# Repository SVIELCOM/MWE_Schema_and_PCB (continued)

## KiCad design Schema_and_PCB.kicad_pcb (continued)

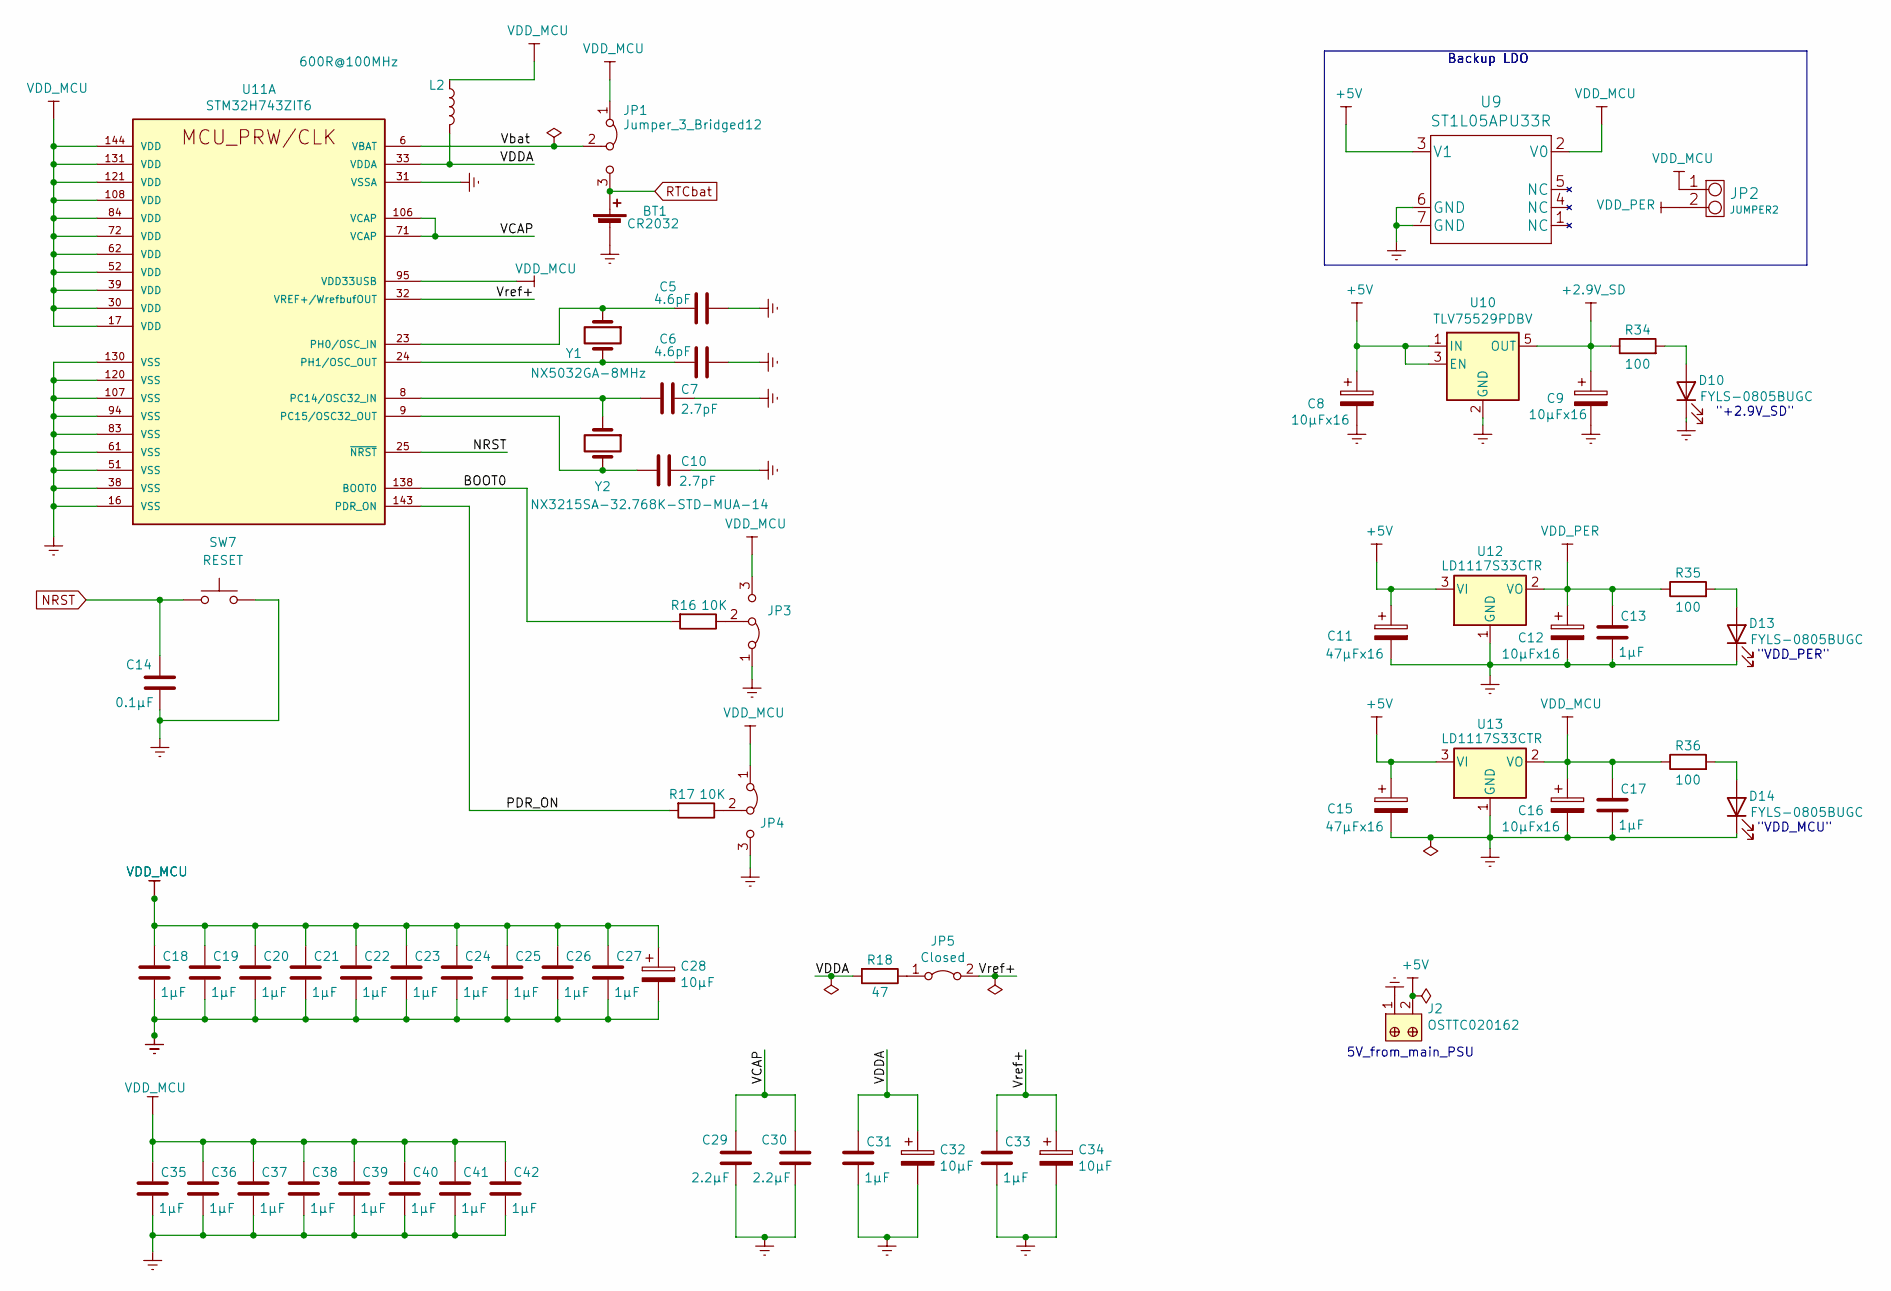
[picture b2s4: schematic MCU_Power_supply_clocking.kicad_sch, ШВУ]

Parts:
BT1: CR2032; BAT_BS-7
C5, C6: 4.6pF; C_0603_1608Metric_Pad1.08x0.95mm_HandSolder
C7, C10: 2.7pF; C_0603_1608Metric_Pad1.08x0.95mm_HandSolder
C8, C9, C12, C16: 10µFx16; CP_EIA-3216-10_Kemet-I
C11, C15: 47µFx16; CP_EIA-7343-31_Kemet-D_Pad2.25x2.55mm_HandSolder
C13, C17, C18, C19, C20, C21, C22, C23, C24, C25, C26, C27, C31, C33, C35, C36, C37, C38, C39, C40, C41, C42: 1µF; C_0603_1608Metric_Pad1.08x0.95mm_HandSolder
C14: 0.1µF; C_0603_1608Metric_Pad1.08x0.95mm_HandSolder
C28, C32, C34: 10µF; CP_EIA-3216-10_Kemet-I
C29, C30: 2.2µF; C_0603_1608Metric_Pad1.08x0.95mm_HandSolder
D10, D13, D14: FYLS-0805BUGC; LED_0805_2012Metric
J2: OSTTC020162; Term_Block_1x2_P5mm; MPN OSTTC020162; Digi-Key_PN ED2600-ND
JP1, JP4: Jumper_3_Bridged12; SolderJumper-3_P1.3mm_Open_RoundedPad1.0x1.5mm_NumberLabels
JP2: JUMPER2; PinHeader_1x02_P2.54mm_Vertical
JP3: BOOT0; PinHeader_1x03_P2.54mm_Horizontal
JP5: Closed; SolderJumper-2_P1.3mm_Open_RoundedPad1.0x1.5mm
L2: 600R@100MHz; L_0805_2012Metric_Pad1.15x1.40mm_HandSolder
R16, R17: 10K; R_0805_2012Metric_Pad1.20x1.40mm_HandSolder
R18: 47; R_0805_2012Metric_Pad1.20x1.40mm_HandSolder
R34, R35, R36: 100; R_0805_2012Metric
SW7: RESET; SW_PUSH_6mm
U9: ST1L05APU33R
U10: TLV75529PDBV; SOT-23-5
U11: STM32H743ZIT6; QFP50P2200X2200X160-144N; PARTREV 7
U12, U13: LD1117S33CTR; SOT-223-3_TabPin2
Y1: NX5032GA-8MHz; Crystal_SMD_5032-2Pin_5.0x3.2mm
Y2: NX3215SA-32.768K-STD-MUA-14; Crystal_SMD_MicroCrystal_CC7V-T1A-2Pin_3.2x1.5mm_HandSolder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

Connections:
+2,9V: C9.1, R34.1, U10.5 (OUT); also elsewhere on the board
/MCU_Power_supply_clocking/BOOT0: R16.2, U11.138 (BOOT0)
/MCU_Power_supply_clocking/PDR_ON: R17.2, U11.143 (PDR_ON)
/MCU_Power_supply_clocking/VCAP: C29.2, C30.2, U11.71 (VCAP), U11.106 (VCAP)
/MCU_Power_supply_clocking/VDDA: C31.1, C32.1, L2.2, R18.2, U11.33 (VDDA)
/MCU_Power_supply_clocking/Vbat: JP1.2 (C), U11.6 (VBAT)
/MCU_Power_supply_clocking/Vref+: C33.1, C34.1, JP5.2 (B), U11.32 (VREF+/WrefbufOUT)
GNDREF: BT1.2 (-), C5.1, C6.1, C7.1, C8.2, C9.2, C10.1, C11.2, C12.2, C13.2, C14.1, C15.2, C16.2, C17.2, C18.2, C19.2, C20.2, C21.2, C22.2, C23.2, C24.2, C25.2, C26.2, C27.2, C28.2, C29.1, C30.1, C31.2, C32.2, C33.2, C34.2, C35.2, C36.2, C37.2, C38.2, C39.2, C40.2, C41.2, C42.2, D10.1 (K), D13.1 (K), D14.1 (K), J2.1, JP3.1 (A), JP4.3 (B), SW7.2, U9.6 (GND), U9.7 (GND), U10.2 (GND), U11.16 (VSS), U11.31 (VSSA), U11.38 (VSS), U11.51 (VSS), U11.61 (VSS), U11.83 (VSS), U11.94 (VSS), U11.107 (VSS), U11.120 (VSS), U11.130 (VSS), U12.1 (GND), U13.1 (GND); also elsewhere on the board
NRST: C14.2, SW7.1, U11.25 (~NRST); also elsewhere on the board
unnamed: C5.2, U11.23 (PH0/OSC_IN), Y1.1
unnamed: C6.2, U11.24 (PH1/OSC_OUT), Y1.2
unnamed: C7.2, U11.8 (PC14/OSC32_IN), Y2.1
unnamed: C10.2, U11.9 (PC15/OSC32_OUT), Y2.2
unnamed: D10.2 (A), R34.2
unnamed: D13.2 (A), R35.2
unnamed: D14.2 (A), R36.2
unnamed: JP3.2 (C), R16.1
unnamed: JP4.2 (C), R17.1
unnamed: JP5.1 (A), R18.1
RTCbat: BT1.1 (+), JP1.3 (B); also elsewhere on the board
VDD_MCU: C16.1, C17.1, C18.1, C19.1, C20.1, C21.1, C22.1, C23.1, C24.1, C25.1, C26.1, C27.1, C28.1, C35.1, C36.1, C37.1, C38.1, C39.1, C40.1, C41.1, C42.1, JP1.1 (A), JP2.1, JP3.3 (B), JP4.1 (A), L2.1, R36.1, U9.2 (V0), U11.17 (VDD), U11.30 (VDD), U11.39 (VDD), U11.52 (VDD), U11.62 (VDD), U11.72 (VDD), U11.84 (VDD), U11.95 (VDD33USB), U11.108 (VDD), U11.121 (VDD), U11.131 (VDD), U11.144 (VDD), U13.2 (VO); also elsewhere on the board
VDD_PER: C12.1, C13.1, JP2.2, R35.1, U12.2 (VO); also elsewhere on the board

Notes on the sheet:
Backup LDO
5V_from_main_PSU
"VDD_PER"
"+2.9V_SD"
"VDD_MCU"

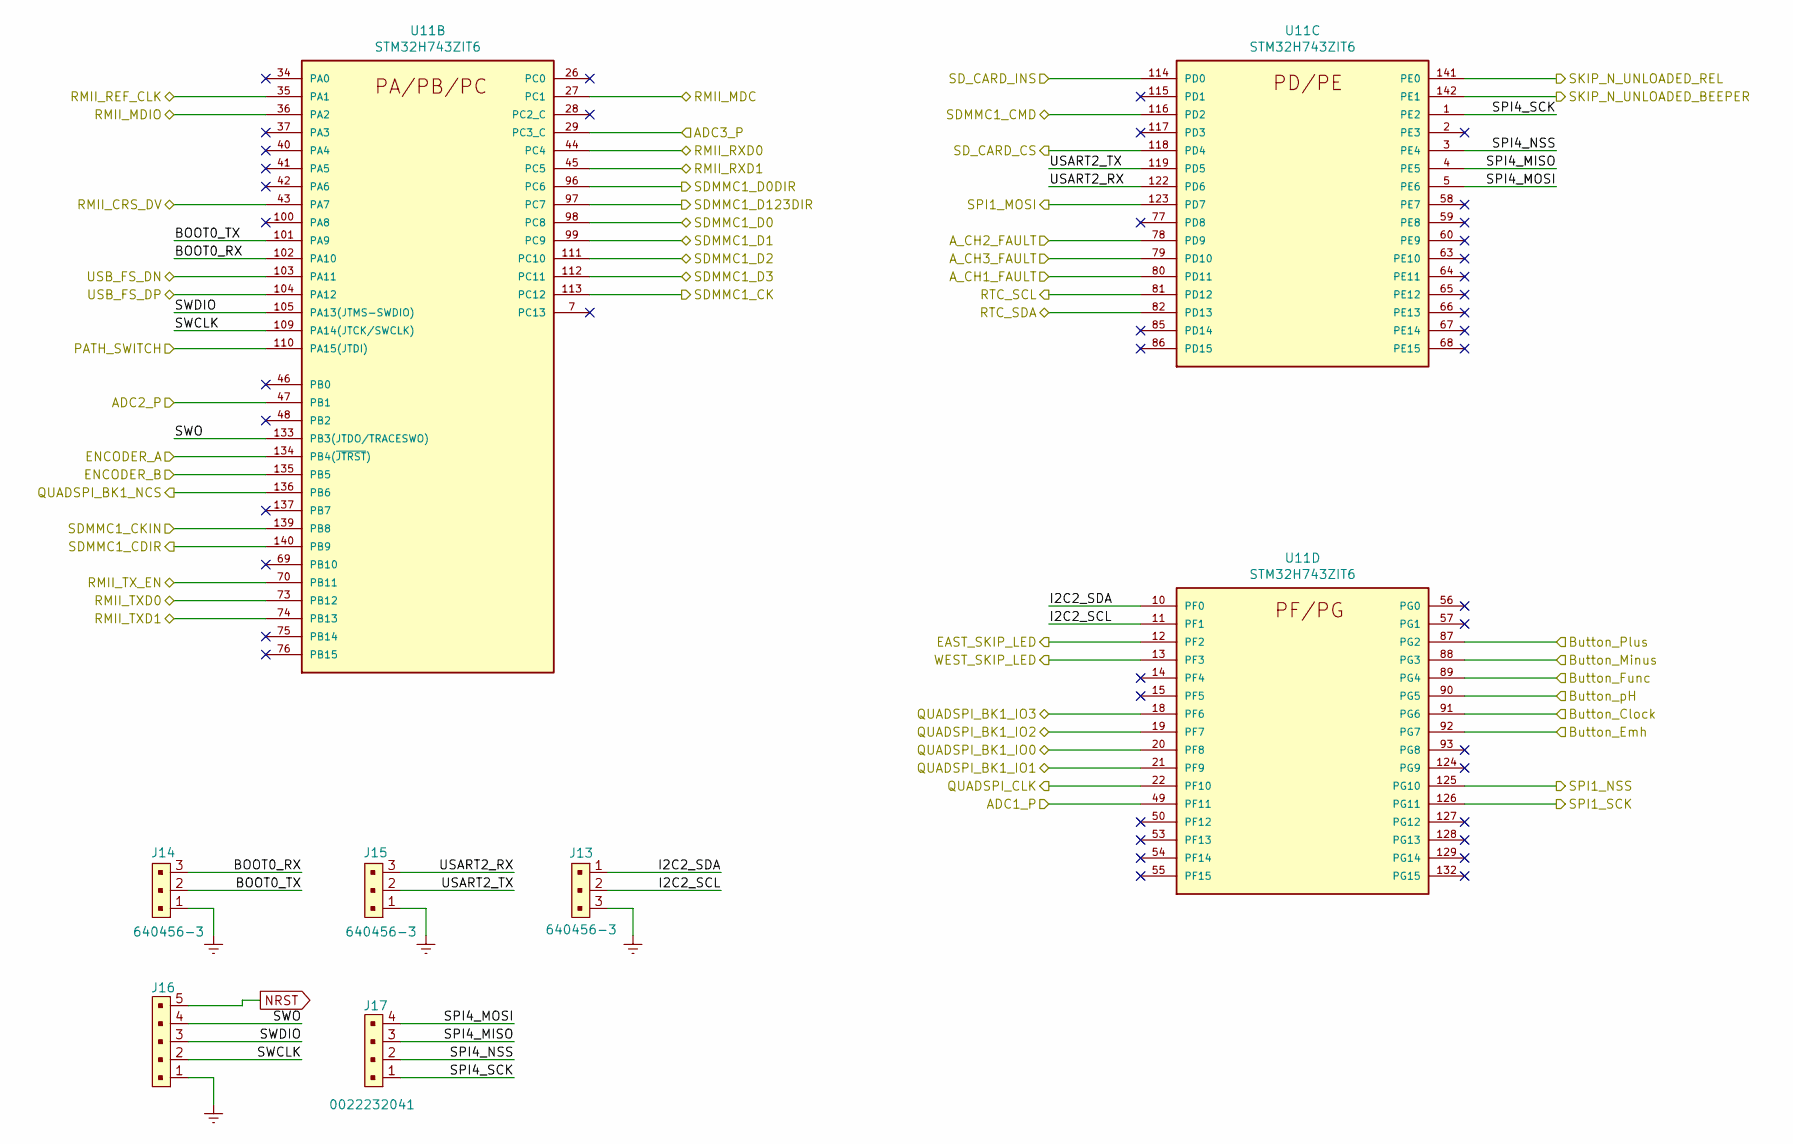
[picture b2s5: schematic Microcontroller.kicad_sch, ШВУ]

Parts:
J13, J14, J15: 640456-3; PinHeader_1x03_P2.54mm_Vertical; MPN 640456-3; Digi-Key_PN A19470-ND
J16: B5B-XH-A_LF__SN_; PinHeader_1x05_P2.54mm_Vertical; MPN B5B-XH-A(LF)(SN); Digi-Key_PN 455-2270-ND
J17: 0022232041; PinHeader_1x04_P2.54mm_Vertical; MPN 0022232041; Digi-Key_PN WM4202-ND
U11: STM32H743ZIT6; QFP50P2200X2200X160-144N; PARTREV 7

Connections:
/Buttons/Button_Clock: U11.91 (PG6); also elsewhere on the board
/Buttons/Button_Emh: U11.92 (PG7); also elsewhere on the board
/Buttons/Button_Func: U11.89 (PG4); also elsewhere on the board
/Buttons/Button_Minus: U11.88 (PG3); also elsewhere on the board
/Buttons/Button_Plus: U11.87 (PG2); also elsewhere on the board
/Buttons/Button_pH: U11.90 (PG5); also elsewhere on the board
/Digital_IO_analog_Inputs/ADC1_P: U11.49 (PF11); also elsewhere on the board
/Digital_IO_analog_Inputs/ADC2_P: U11.47 (PB1); also elsewhere on the board
/Digital_IO_analog_Inputs/ADC3_P: U11.29 (PC3_C); also elsewhere on the board
/Digital_IO_analog_Inputs/A_CH1_FAULT: U11.77 (PD8); also elsewhere on the board
/Digital_IO_analog_Inputs/A_CH2_FAULT: U11.75 (PB14); also elsewhere on the board
/Digital_IO_analog_Inputs/A_CH3_FAULT: U11.76 (PB15); also elsewhere on the board
/Digital_IO_analog_Inputs/ENCODER_A: U11.134 (PB4(~JTRST)); also elsewhere on the board
/Digital_IO_analog_Inputs/ENCODER_B: U11.135 (PB5); also elsewhere on the board
/Digital_IO_analog_Inputs/LEVEL_SWITCH: U11.110 (PA15(JTDI)); also elsewhere on the board
/Digital_IO_analog_Inputs/SKIP_N_UNLOADED_BEEPER: U11.142 (PE1); also elsewhere on the board
/Digital_IO_analog_Inputs/SKIP_N_UNLOADED_REL: U11.141 (PE0); also elsewhere on the board
/Indicator/EAST_SKIP_LED: U11.12 (PF2); also elsewhere on the board
/Indicator/SPI1_MOSI: U11.123 (PD7); also elsewhere on the board
/Indicator/SPI1_NSS: U11.125 (PG10); also elsewhere on the board
/Indicator/SPI1_SCK: U11.126 (PG11); also elsewhere on the board
/Indicator/WEST_SKIP_LED: U11.13 (PF3); also elsewhere on the board
/LAN/RMII_CRS_DV: U11.43 (PA7); also elsewhere on the board
/LAN/RMII_MDC: U11.27 (PC1); also elsewhere on the board
/LAN/RMII_MDIO: U11.36 (PA2); also elsewhere on the board
/LAN/RMII_REF_CLK: U11.35 (PA1); also elsewhere on the board
/LAN/RMII_RXD0: U11.44 (PC4); also elsewhere on the board
/LAN/RMII_RXD1: U11.45 (PC5); also elsewhere on the board
/LAN/RMII_TXD0: U11.73 (PB12); also elsewhere on the board
/LAN/RMII_TXD1: U11.74 (PB13); also elsewhere on the board
/LAN/RMII_TX_EN: U11.70 (PB11); also elsewhere on the board
/Microcontroller/BOOT0_RX: J14.3, U11.102 (PA10)
/Microcontroller/BOOT0_TX: J14.2, U11.101 (PA9)
/Microcontroller/I2C2_SCL: J13.2, U11.11 (PF1)
/Microcontroller/I2C2_SDA: J13.1, U11.10 (PF0)
/Microcontroller/QUADSPI_BK1_NCS: U11.136 (PB6); also elsewhere on the board
/Microcontroller/QUADSPI_CLK: U11.22 (PF10); also elsewhere on the board
/Microcontroller/RTC_SCL: U11.81 (PD12); also elsewhere on the board
/Microcontroller/RTC_SDA: U11.82 (PD13); also elsewhere on the board
/Microcontroller/SDMMC1_CDIR: U11.140 (PB9); also elsewhere on the board
/Microcontroller/SDMMC1_CK: U11.113 (PC12); also elsewhere on the board
/Microcontroller/SDMMC1_CKIN: U11.139 (PB8); also elsewhere on the board
/Microcontroller/SDMMC1_CMD: U11.116 (PD2); also elsewhere on the board
/Microcontroller/SDMMC1_D0: U11.98 (PC8); also elsewhere on the board
/Microcontroller/SDMMC1_D0DIR: U11.96 (PC6); also elsewhere on the board
/Microcontroller/SDMMC1_D1: U11.99 (PC9); also elsewhere on the board
/Microcontroller/SDMMC1_D2: U11.111 (PC10); also elsewhere on the board
/Microcontroller/SDMMC1_D3: U11.112 (PC11); also elsewhere on the board
/Microcontroller/SDMMC1_D123DIR: U11.97 (PC7); also elsewhere on the board
/Microcontroller/SD_CARD_CS: U11.118 (PD4); also elsewhere on the board
/Microcontroller/SD_CARD_INS: U11.117 (PD3); also elsewhere on the board
/Microcontroller/SPI4_MISO: J17.3, U11.4 (PE5)
/Microcontroller/SPI4_MOSI: J17.4, U11.5 (PE6)
/Microcontroller/SPI4_NSS: J17.2, U11.3 (PE4)
/Microcontroller/SPI4_SCK: J17.1, U11.1 (PE2)
/Microcontroller/SWCLK: J16.2, U11.109 (PA14(JTCK/SWCLK))
/Microcontroller/SWDIO: J16.3, U11.105 (PA13(JTMS-SWDIO))
/Microcontroller/SWO: J16.4, U11.133 (PB3(JTDO/TRACESWO))
/Microcontroller/USART2_RX: J15.3, U11.122 (PD6)
/Microcontroller/USART2_TX: J15.2, U11.119 (PD5)
/Microcontroller/USB_FS_DN: U11.103 (PA11); also elsewhere on the board
/Microcontroller/USB_FS_DP: U11.104 (PA12); also elsewhere on the board
/Storage_and_memory/QUADPSI_BK1_IO0: U11.20 (PF8); also elsewhere on the board
/Storage_and_memory/QUADPSI_BK1_IO1: U11.21 (PF9); also elsewhere on the board
/Storage_and_memory/QUADPSI_BK1_IO2: U11.19 (PF7); also elsewhere on the board
/Storage_and_memory/QUADPSI_BK1_IO3: U11.18 (PF6); also elsewhere on the board
GNDREF: J13.3, J14.1, J15.1, J16.1; also elsewhere on the board
NRST: J16.5; also elsewhere on the board

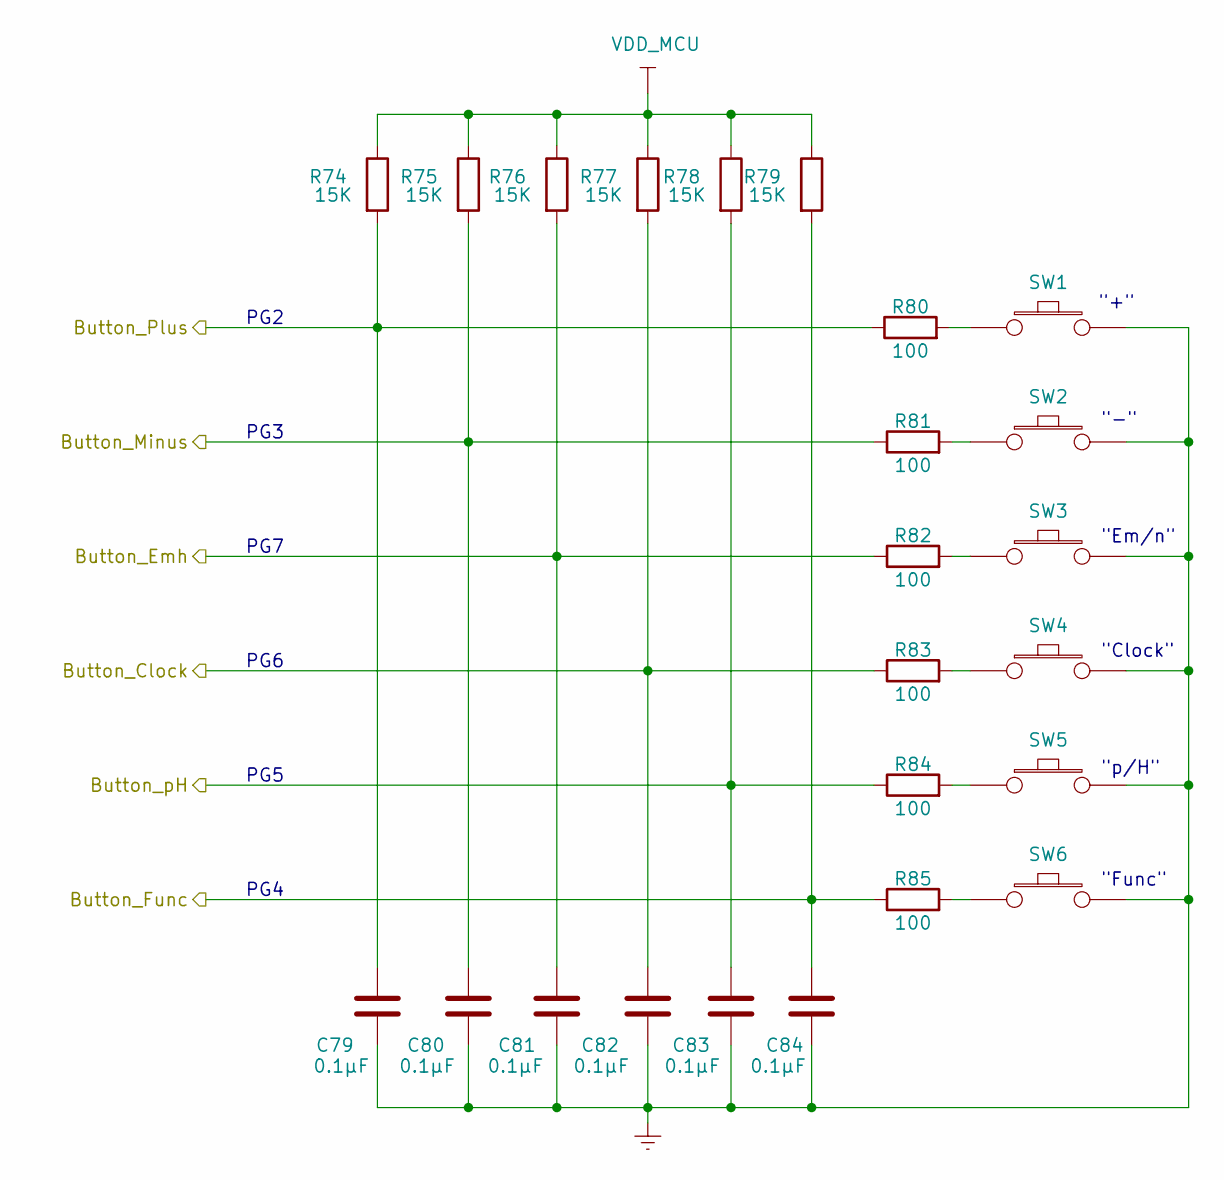
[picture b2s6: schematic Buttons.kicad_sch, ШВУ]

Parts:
C79, C80, C81, C82, C83, C84: 0.1µF; C_0603_1608Metric_Pad1.08x0.95mm_HandSolder
R74, R75, R76, R77, R78, R79: 15K; R_0805_2012Metric_Pad1.20x1.40mm_HandSolder
R80, R81, R82, R83, R84, R85: 100; R_0805_2012Metric_Pad1.20x1.40mm_HandSolder
SW1, SW2, SW3, SW4, SW5, SW6: SW_PUSHBUTTON; PinHeader_1x2_P2.54mm

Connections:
/Buttons/Button_Clock: C82.1, R77.2, R83.1; also elsewhere on the board
/Buttons/Button_Emh: C81.1, R76.2, R82.1; also elsewhere on the board
/Buttons/Button_Func: C84.1, R79.2, R85.1; also elsewhere on the board
/Buttons/Button_Minus: C80.1, R75.2, R81.1; also elsewhere on the board
/Buttons/Button_Plus: C79.1, R74.2, R80.1; also elsewhere on the board
/Buttons/Button_pH: C83.1, R78.2, R84.1; also elsewhere on the board
GNDREF: C79.2, C80.2, C81.2, C82.2, C83.2, C84.2, SW1.2, SW2.2, SW3.2, SW4.2, SW5.2, SW6.2; also elsewhere on the board
unnamed: R80.2, SW1.1
unnamed: R81.2, SW2.1
unnamed: R82.2, SW3.1
unnamed: R83.2, SW4.1
unnamed: R84.2, SW5.1
unnamed: R85.2, SW6.1
VDD_MCU: R74.1, R75.1, R76.1, R77.1, R78.1, R79.1; also elsewhere on the board

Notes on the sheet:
"Func"
PG4
"Em/n"
PG7
"+"
"p/H"
PG6
PG3
"Clock"
PG5
"-"
PG2

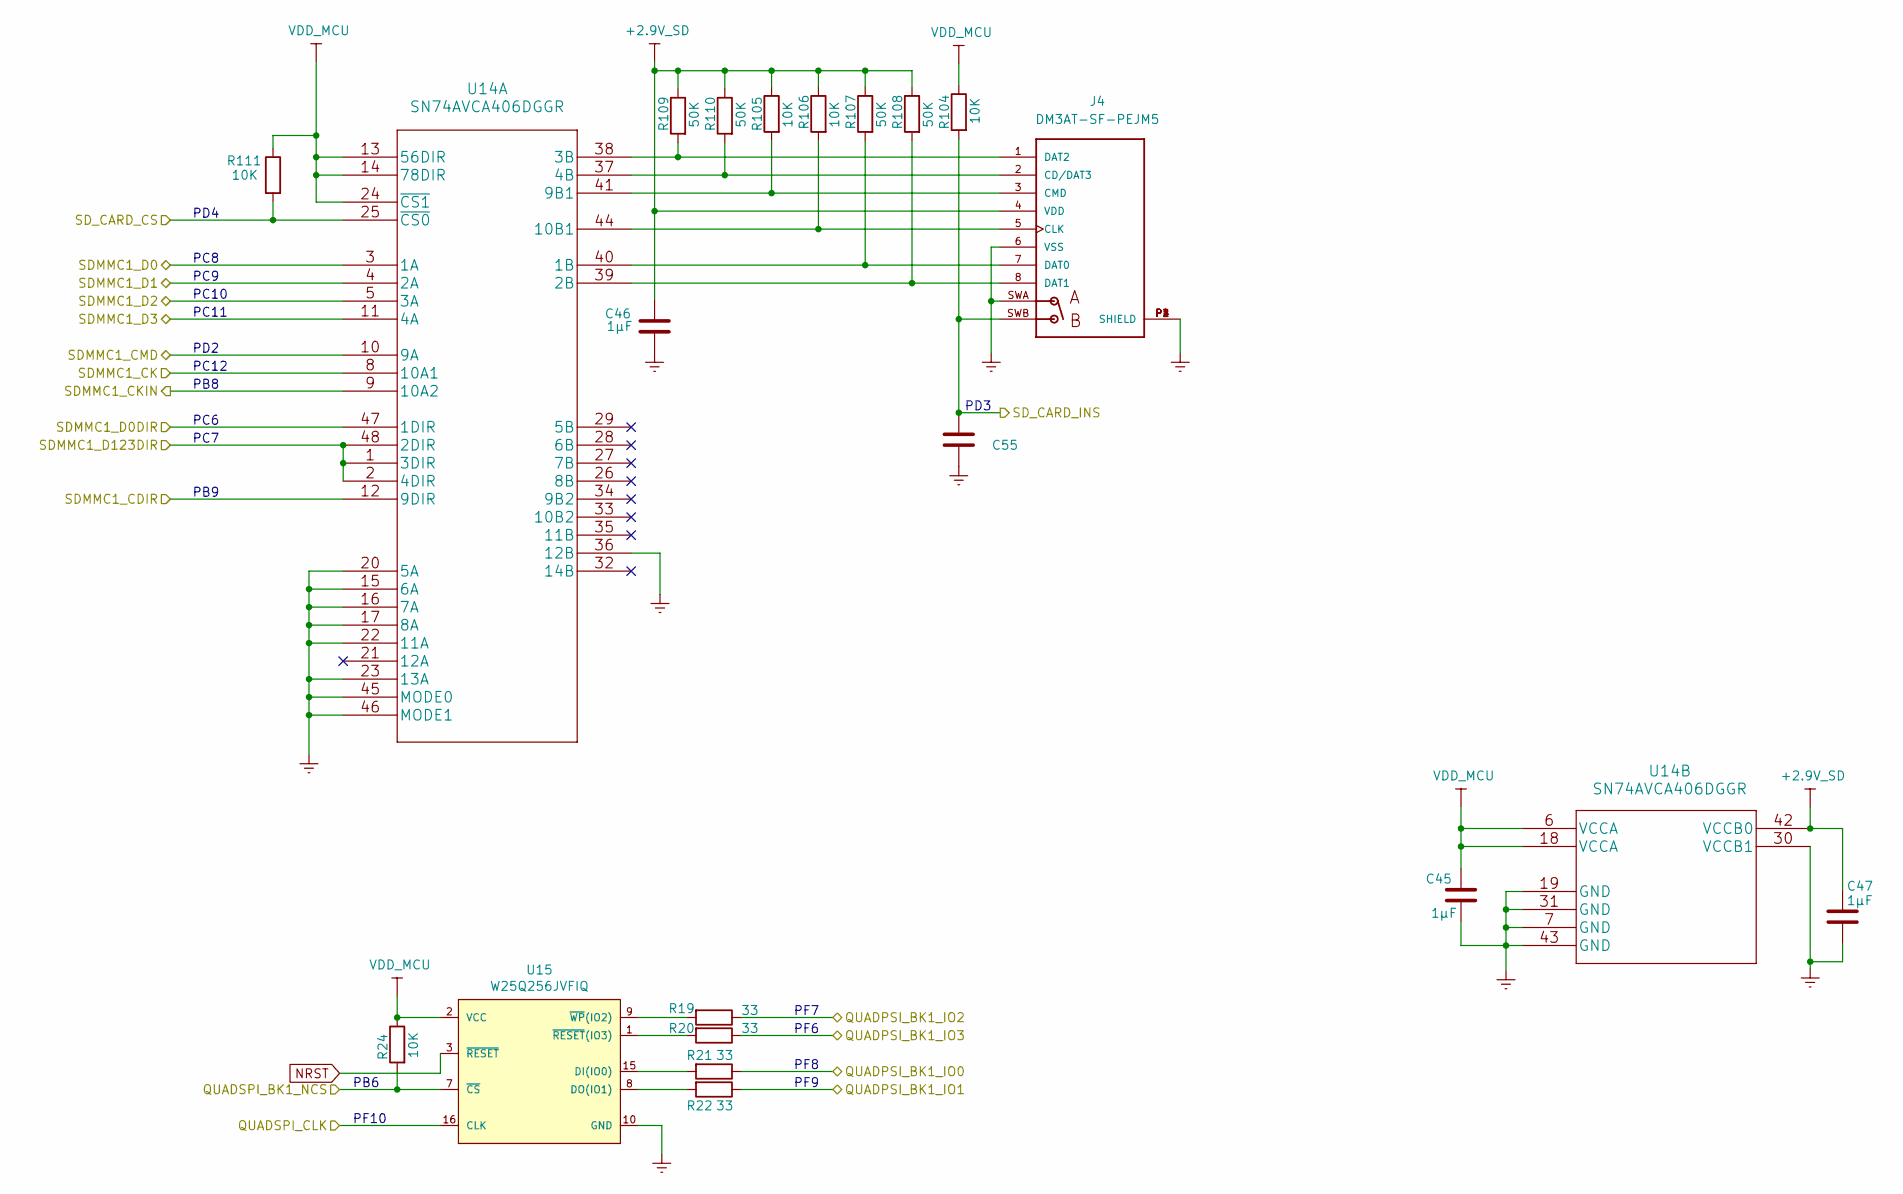
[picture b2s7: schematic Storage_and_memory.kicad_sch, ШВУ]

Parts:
C45, C46, C47: 1µF; C_0603_1608Metric_Pad1.08x0.95mm_HandSolder
C55: (no value)
J4: DM3AT-SF-PEJM5; HRS_DM3AT-SF-PEJM5
R19, R20, R21, R22: 33; R_0805_2012Metric
R24: 10K; R_0805_2012Metric_Pad1.20x1.40mm_HandSolder
R104, R105, R106, R111: 10K; R_0805_2012Metric
R107, R108, R109, R110: 50K; R_0805_2012Metric
U14: SN74AVCA406DGGR
U15: W25Q256JVFIQ; SOIC-16W_7.5x10.3mm_P1.27mm; digikey description IC FLASH 256MBIT 104MHZ 16WSOIC

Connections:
+2,9V: C46.1, C47.1, J4.4 (VDD), R105.1, R106.1, R107.1, R108.1, R109.1, R110.1, U14.42 (VCCB0); also elsewhere on the board
/Microcontroller/QUADSPI_BK1_NCS: R24.2, U15.7 (~CS); also elsewhere on the board
/Microcontroller/QUADSPI_CLK: U15.16 (CLK); also elsewhere on the board
/Microcontroller/SDMMC1_CDIR: U14.12 (9DIR); also elsewhere on the board
/Microcontroller/SDMMC1_CK: U14.8 (10A1); also elsewhere on the board
/Microcontroller/SDMMC1_CKIN: U14.9 (10A2); also elsewhere on the board
/Microcontroller/SDMMC1_CMD: U14.10 (9A); also elsewhere on the board
/Microcontroller/SDMMC1_D0: U14.3 (1A); also elsewhere on the board
/Microcontroller/SDMMC1_D0DIR: U14.47 (1DIR); also elsewhere on the board
/Microcontroller/SDMMC1_D1: U14.4 (2A); also elsewhere on the board
/Microcontroller/SDMMC1_D2: U14.5 (3A); also elsewhere on the board
/Microcontroller/SDMMC1_D3: U14.11 (4A); also elsewhere on the board
/Microcontroller/SDMMC1_D123DIR: U14.1 (3DIR), U14.2 (4DIR), U14.48 (2DIR); also elsewhere on the board
/Microcontroller/SD_CARD_CS: R111.2, U14.25 (~CS0); also elsewhere on the board
/Microcontroller/SD_CARD_INS: C55.1, J4.SWB, R104.2; also elsewhere on the board
/Storage_and_memory/QUADPSI_BK1_IO0: R21.1; also elsewhere on the board
/Storage_and_memory/QUADPSI_BK1_IO1: R22.1; also elsewhere on the board
/Storage_and_memory/QUADPSI_BK1_IO2: R19.1; also elsewhere on the board
/Storage_and_memory/QUADPSI_BK1_IO3: R20.1; also elsewhere on the board
GNDREF: C45.2, C46.2, C47.2, C55.2, J4.6 (VSS), J4.P1 (SHIELD), J4.P2 (SHIELD), J4.P3 (SHIELD), J4.P4 (SHIELD), J4.SWA, U14.7 (GND), U14.15 (6A), U14.16 (7A), U14.17 (8A), U14.19 (GND), U14.20 (5A), U14.22 (11A), U14.23 (13A), U14.30 (VCCB1), U14.31 (GND), U14.36 (12B), U14.43 (GND), U14.45 (MODE0), U14.46 (MODE1), U15.10 (GND); also elsewhere on the board
NRST: U15.3 (~RESET); also elsewhere on the board
unnamed: J4.1 (DAT2), R109.2, U14.38 (3B)
unnamed: J4.2 (CD/DAT3), R110.2, U14.37 (4B)
unnamed: J4.3 (CMD), R105.2, U14.41 (9B1)
unnamed: J4.5 (CLK), R106.2, U14.44 (10B1)
unnamed: J4.7 (DAT0), R107.2, U14.40 (1B)
unnamed: J4.8 (DAT1), R108.2, U14.39 (2B)
unnamed: R19.2, U15.9 (~WP(IO2))
unnamed: R20.2, U15.1 (~RESET(IO3))
unnamed: R21.2, U15.15 (DI(IO0))
unnamed: R22.2, U15.8 (DO(IO1))
VDD_MCU: C45.1, R24.1, R104.1, R111.1, U14.6 (VCCA), U14.13 (56DIR), U14.14 (78DIR), U14.18 (VCCA), U14.24 (~CS1), U15.2 (VCC); also elsewhere on the board

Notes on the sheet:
PF10
PD3
PC8
PB6
PC9
PF7
PF8
PF9
PD4
PC12
PF6
PD2
PB9
PC11
PB8
PC7
PC6
PC10

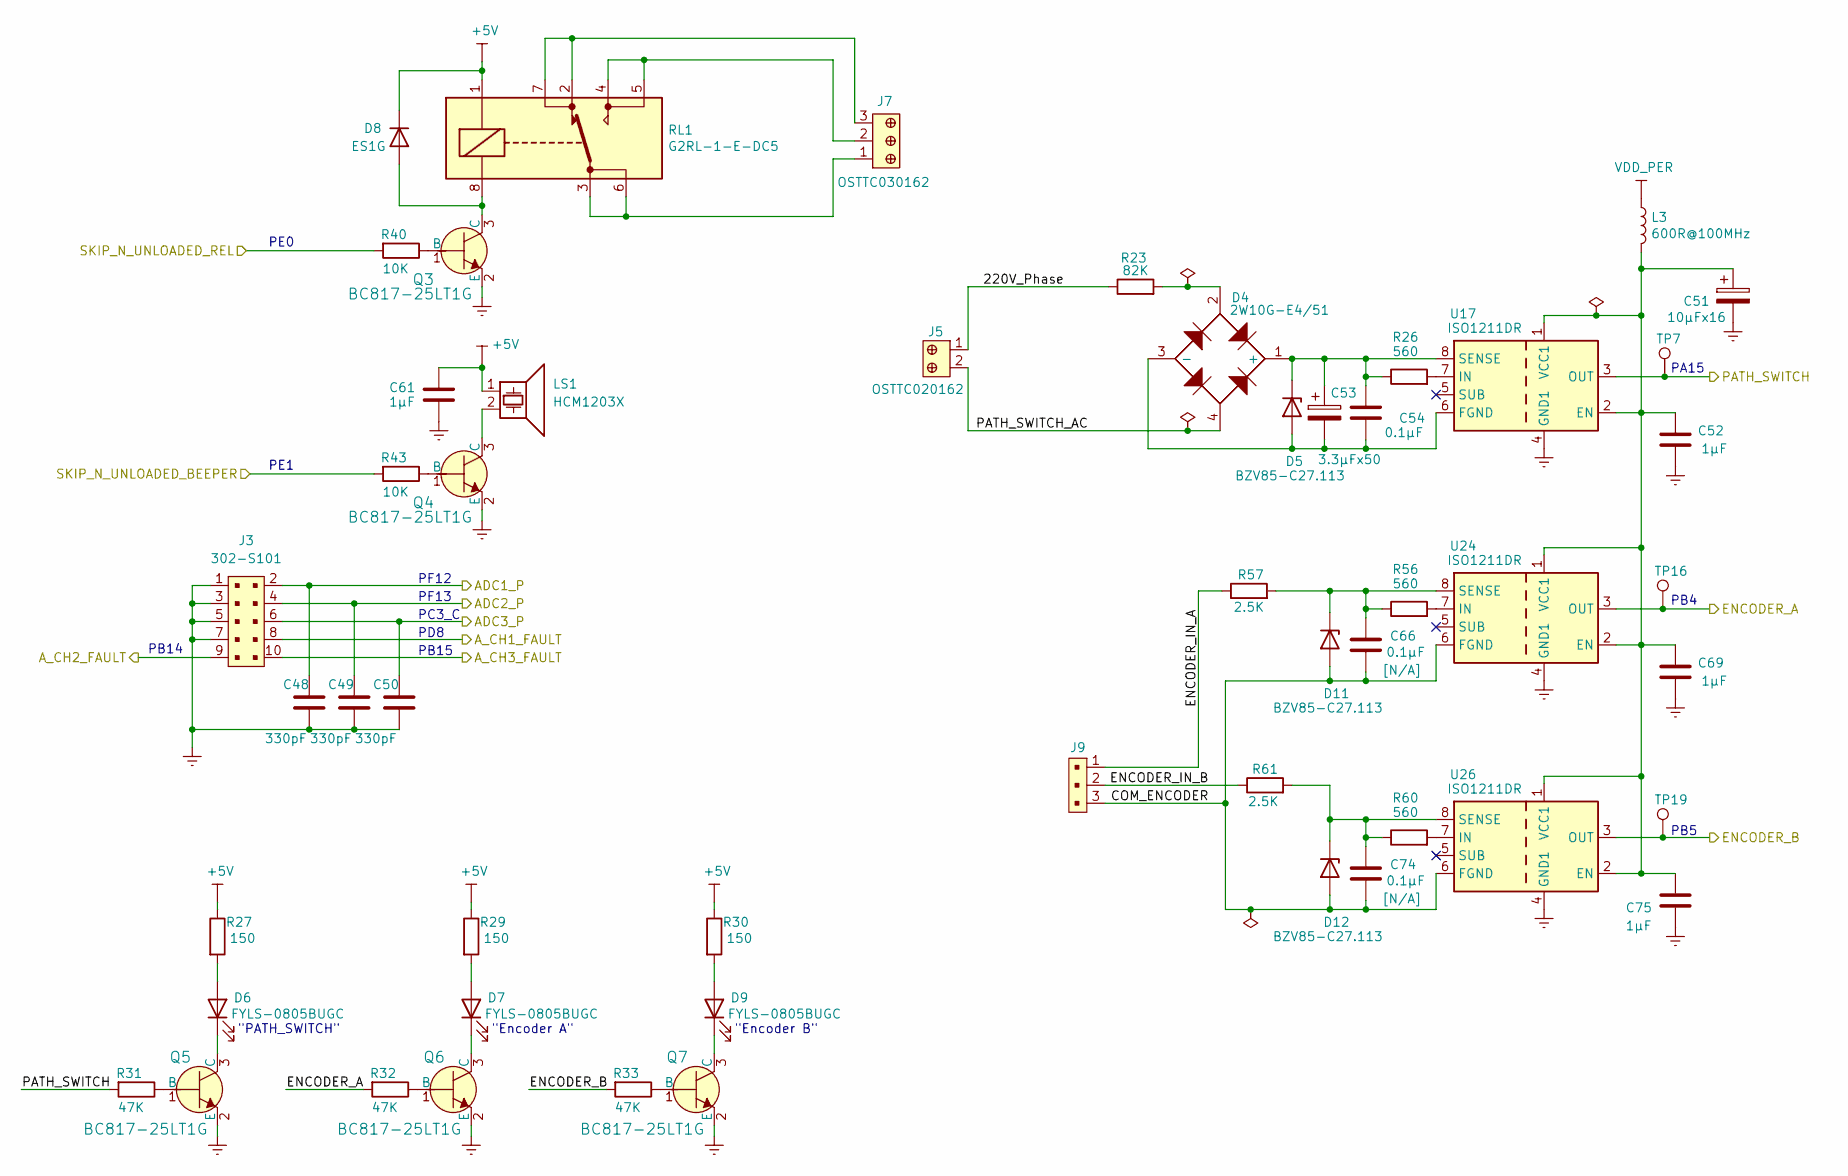
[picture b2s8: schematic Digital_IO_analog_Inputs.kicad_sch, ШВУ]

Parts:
C48, C49, C50: 330pF; C_0603_1608Metric_Pad1.08x0.95mm_HandSolder
C51: 10µFx16; CP_EIA-3216-10_Kemet-I
C52, C61, C69, C75: 1µF; C_0603_1608Metric_Pad1.08x0.95mm_HandSolder
C53: 3.3µFx50; CP_EIA-6032-15_Kemet-U
C54, C66, C74: 0.1µF; C_0603_1608Metric_Pad1.08x0.95mm_HandSolder
D4: 2W10G-E4/51; Diode_Bridge_Round_D9.8mm
D5, D11, D12: BZV85-C27.113; D_DO-41_SOD81_P10.16mm_Horizontal
D6, D7, D9: FYLS-0805BUGC; LED_0805_2012Metric
D8: ES1G; D_SMA_Handsoldering
J3: 302-S101; PinHeader_2x5_P2.54mm_Drill1.2mm; MPN 302-S101; Digi-Key_PN ED1543-ND
J5: OSTTC020162; Term_Block_1x2_P5mm; MPN OSTTC020162; Digi-Key_PN ED2600-ND
J7: OSTTC030162; Term_Block_1x3_P5mm; MPN OSTTC030162; Digi-Key_PN ED2601-ND
J9: 0022232031; PinHeader_1x3_P2.54mm_Drill1.02mm; MPN 0022232031; Digi-Key_PN WM4201-ND
L3: 600R@100MHz; L_0805_2012Metric_Pad1.15x1.40mm_HandSolder
LS1: HCM1203X; Buzzer_12x9.5RM7.6
Q3, Q4, Q5, Q6, Q7: BC817-25LT1G; SOT-23-3; MPN BC817-25LT1G; Digi-Key_PN BC817-25LT1GOSCT-ND
R23: 82K; R_Axial_DIN0207_L6.3mm_D2.5mm_P10.16mm_Horizontal
R26, R56, R60: 560; R_0805_2012Metric_Pad1.20x1.40mm_HandSolder
R27, R29, R30: 150; R_0805_2012Metric_Pad1.20x1.40mm_HandSolder
R31, R32, R33: 47K; R_0805_2012Metric_Pad1.20x1.40mm_HandSolder
R40, R43: 10K; R_0805_2012Metric_Pad1.20x1.40mm_HandSolder
R57, R61: 2.5K; R_Axial_DIN0207_L6.3mm_D2.5mm_P10.16mm_Horizontal
RL1: G2RL-1-E-DC5; Relay_DPDT_Omron_G2RL
TP7, TP16, TP19: TestPoint; TestPoint_Pad_D1.5mm
U17, U24, U26: ISO1211DR; SOIC-8_3.9x4.9mm_P1.27mm

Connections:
/Digital_IO_analog_Inputs/220V_Phase: J5.1, R23.1
/Digital_IO_analog_Inputs/ADC1_P: C48.1, J3.2; also elsewhere on the board
/Digital_IO_analog_Inputs/ADC2_P: C49.1, J3.4; also elsewhere on the board
/Digital_IO_analog_Inputs/ADC3_P: C50.1, J3.6; also elsewhere on the board
/Digital_IO_analog_Inputs/A_CH1_FAULT: J3.8; also elsewhere on the board
/Digital_IO_analog_Inputs/A_CH2_FAULT: J3.9; also elsewhere on the board
/Digital_IO_analog_Inputs/A_CH3_FAULT: J3.10; also elsewhere on the board
/Digital_IO_analog_Inputs/ENCODER_A: TP16.1, U24.3 (OUT); also elsewhere on the board
/Digital_IO_analog_Inputs/ENCODER_B: TP19.1, U26.3 (OUT); also elsewhere on the board
/Digital_IO_analog_Inputs/LEVEL_SWITCH: TP7.1, U17.3 (OUT); also elsewhere on the board
/Digital_IO_analog_Inputs/LEVEL_SWITCH_AC: D4.4, J5.2
/Digital_IO_analog_Inputs/SKIP_N_UNLOADED_BEEPER: R43.2; also elsewhere on the board
/Digital_IO_analog_Inputs/SKIP_N_UNLOADED_REL: R40.2; also elsewhere on the board
GNDREF: C48.2, C49.2, C50.2, C51.2, C52.2, C61.2, C69.2, C75.2, J3.1, J3.3, J3.5, J3.7, Q3.2 (E), Q4.2 (E), Q5.2 (E), Q6.2 (E), Q7.2 (E), U17.4 (GND1), U24.4 (GND1), U26.4 (GND1); also elsewhere on the board
unnamed: C51.1, C52.1, C69.1, C75.1, L3.2, U17.1 (VCC1), U17.2 (EN), U24.1 (VCC1), U24.2 (EN), U26.1 (VCC1), U26.2 (EN)
unnamed: D4.2, R23.2
unnamed: D6.1 (K), Q5.3 (C)
unnamed: D7.1 (K), Q6.3 (C)
unnamed: D7.2 (A), R29.2
unnamed: D8.2 (A), Q3.3 (C), RL1.8
unnamed: D9.1 (K), Q7.3 (C)
unnamed: D9.2 (A), R30.2
unnamed: J7.1, RL1.3, RL1.6
unnamed: J7.2, RL1.4, RL1.5
unnamed: J7.3, RL1.2, RL1.7
unnamed: LS1.2, Q4.3 (C)
unnamed: Q3.1 (B), R40.1
unnamed: Q4.1 (B), R43.1
unnamed: Q5.1 (B), R31.1
unnamed: Q6.1 (B), R32.1
unnamed: Q7.1 (B), R33.1
unnamed: R26.2, U17.7 (IN)
unnamed: R56.2, U24.7 (IN)
unnamed: R60.2, U26.7 (IN)
VDD_PER: L3.1; also elsewhere on the board

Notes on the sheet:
PE1
PD8
"Encoder A"
PF13
PF12
PA15
PB15
PB14
"PATH_SWITCH"
PE0
PB5
PB4
"Encoder B"
PC3_C

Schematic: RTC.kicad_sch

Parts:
R25, R28: 50; R_0603_1608Metric_Pad0.98x0.95mm_HandSolder
U16: DS3231MZ; SOIC-8_3.9x4.9mm_P1.27mm

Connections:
/Microcontroller/RTC_SCL: R25.2, U16.8 (SCL); also elsewhere on the board
/Microcontroller/RTC_SDA: R28.2, U16.7 (SDA); also elsewhere on the board
GNDREF: U16.5 (GND); also elsewhere on the board
NRST: U16.4 (~RST); also elsewhere on the board
RTCbat: U16.6 (VBAT); also elsewhere on the board
VDD_MCU: R25.1, R28.1, U16.2 (VCC); also elsewhere on the board

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
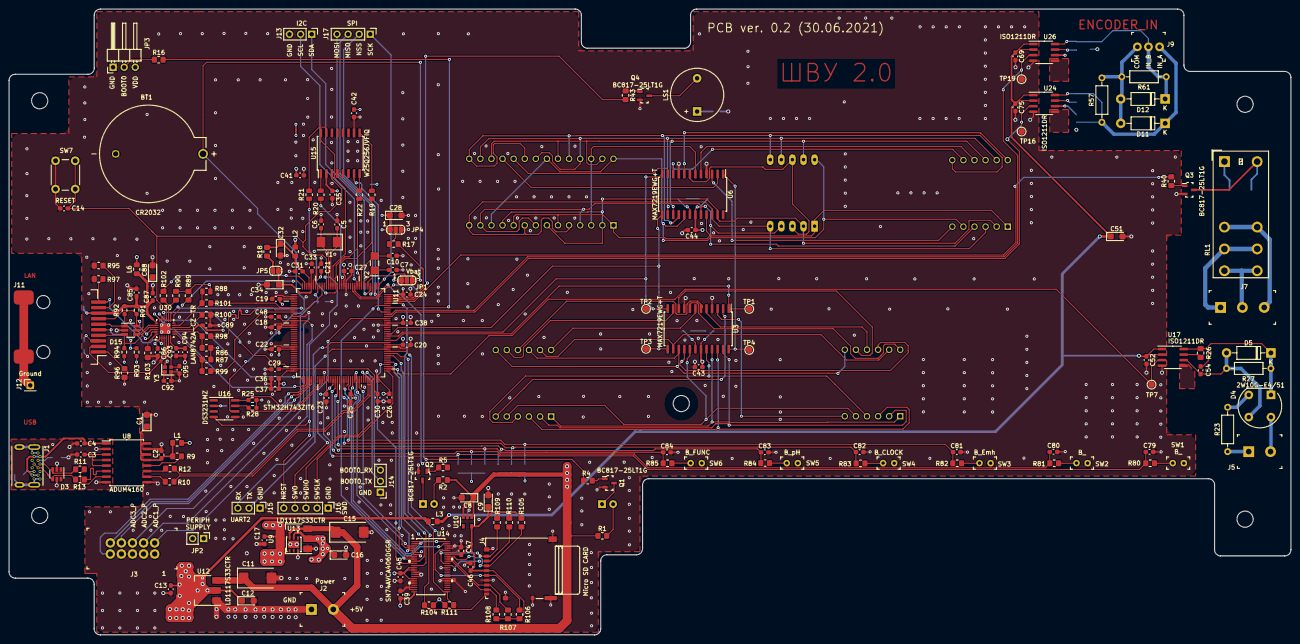
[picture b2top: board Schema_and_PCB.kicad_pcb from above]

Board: 4 copper layers, 293.6 x 143.3 mm, 223 parts (0 on the bottom side), 196 nets.

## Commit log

2021-05-07 Start with huge changes
2021-05-08 Added SD_Card Tranceiver TXS0206-29. Deleted2.9V LDO
2021-05-08 Autosave
2021-05-08 Restore 2.9V LDO
2021-05-08 QSPI and storage sheet finished
2021-05-08 Indication edit
2021-05-09 Indication edit end
2021-05-12 start create Analog IO
2021-05-14 Analog Input edited
2021-05-14 2.9V LDO changed
2021-05-14 ISO1211
2021-05-17 Digital IO ended
2021-05-17 Created scheets Microcontroller, Main power, buttons
2021-05-17 Buttons complete
2021-05-17 analog IO MCU pin named
2021-05-17 begin MCU editing
2021-05-18 Probably pre-alpha version is done
2021-05-18 v0.1
2021-05-19 v0.2 added ecoder inputs
2021-05-19 v0.3 changed sd_card holder
2021-05-20 footprints associations is done
2021-05-21 board setup is done
2021-05-21 board shape is done
2021-05-21 LAN8742 footprint corrected
2021-05-23 starting PCB layout
2021-05-24 corrected few footprints, correct all resistors and capacitors type for ordering
2021-05-25 corrected footprint for B82790C0225N265
2021-05-25 PCB layout continue with SD_CARD interface TXS0206
2021-05-26 deleted TXS0206 added SN74AVCA406DGGR and corrected schema for it
2021-05-26 Generated new netlist
2021-05-26 Prepare to move analog decoupling to standalone PCB
2021-05-26 Remove DigitalIO from Analog decoupling
2021-05-26 Create Analog decoupling PCB
2021-05-26 Analog decoupling PCB dimensions done
2021-05-26 Analog decoupling annotations and create netlist
2021-05-26 Analog decoupling elements place to PCB
2021-05-26 Analog decoupling schema completed. Digital_IO completed and clean up
2021-05-26 main PCB changes
2021-05-27 Footprints for pinheaders changed
2021-05-27 LAN elements placed
2021-05-27 ISO1211 power supply apdated. Label USB_GND added
2021-05-27 PCB autorouting attempt
2021-05-27 PCB drawing
2021-05-31 PCB layout
2021-05-31 Change ADC3 input chanel and pin
2021-06-01 Indicators layout finished
2021-06-01 Draft PCB done
2021-06-01 PCB minor changes
2021-06-02 PCB before Gerber creating
2021-06-03 main PCB done. Gerbers sent to manufacturer
2021-06-04 All vias changed
2021-06-04 All mounting holes changed
2021-06-04 PCB errors correcting
2021-06-07 Main PCB layout done. Order sent to manufacturer
2021-06-08 Analog decoupling PCB layout done. Order sent to manufacturer
2021-06-11 minor changes and add NRST to J16
2021-06-17 SPI6 changed to SPI1
2021-06-29 Commit before correcting mistakes OA pinout in analog decoupling
2021-06-30 OA pinout corrected. Mounting holes deleted
2021-06-30 All mistakes corrected
2021-07-01 minor changes
2021-07-06 NRST to QSPI Flash Reset pin has been connected
2021-10-04 Pined pin_1 U14
2021-10-29 added gitignore
2021-10-29 before accepting symbol updates
2021-10-29 commit after KiCAD library updates
2021-11-18 ADC1 input changed from IN6 to IN2
2021-11-19 More GND vias
2021-11-19 RTC sheet added
2021-11-19 RTC DS3231 layot finished
2021-11-22 USART2 connector connectings redrawed
2021-11-22 Some GND vias added
2021-12-13 ADC2 in changed to IN5
2022-01-18 KiCAD 6 firs saves
2022-02-11 KiCAD6.0 scheema rules check done
2022-02-11 KiCAD6.0 PCB rules check done
2022-02-11 digital inputs refactoring
2022-02-11 Indication LEDs added
2022-02-11 PCB ver. 0.3
2022-02-12 some corrected
2022-02-20 State before converting analog docoupling scheema to KiCAD6.0 format
2022-02-21 Analog decoupling scheema converted to KiCAD6 format. Added LDOs for ISO224. Added power LEDs
2022-02-21 Analog decoupling PCB converted to KiCAD6 format and pass DRC
2022-02-22 Analog decoupling PCB added LDOs for ISO224, added power LEDs
2022-02-22 Analog decoupling PCB J4 and J5 moved to left edge
2022-03-23 GPIO port changed for input signals
2022-03-24 External connectors sheet added
2022-03-24 Skip unload COM signal of external connector corrected
2022-03-24 CPU programming external connector added
2022-07-06 Backup 06.07.2022
2022-07-25 All handsolder footprints removed
